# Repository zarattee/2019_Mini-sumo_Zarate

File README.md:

# 2019_Mini sumo_Zarate
 placa para robot mini sumo

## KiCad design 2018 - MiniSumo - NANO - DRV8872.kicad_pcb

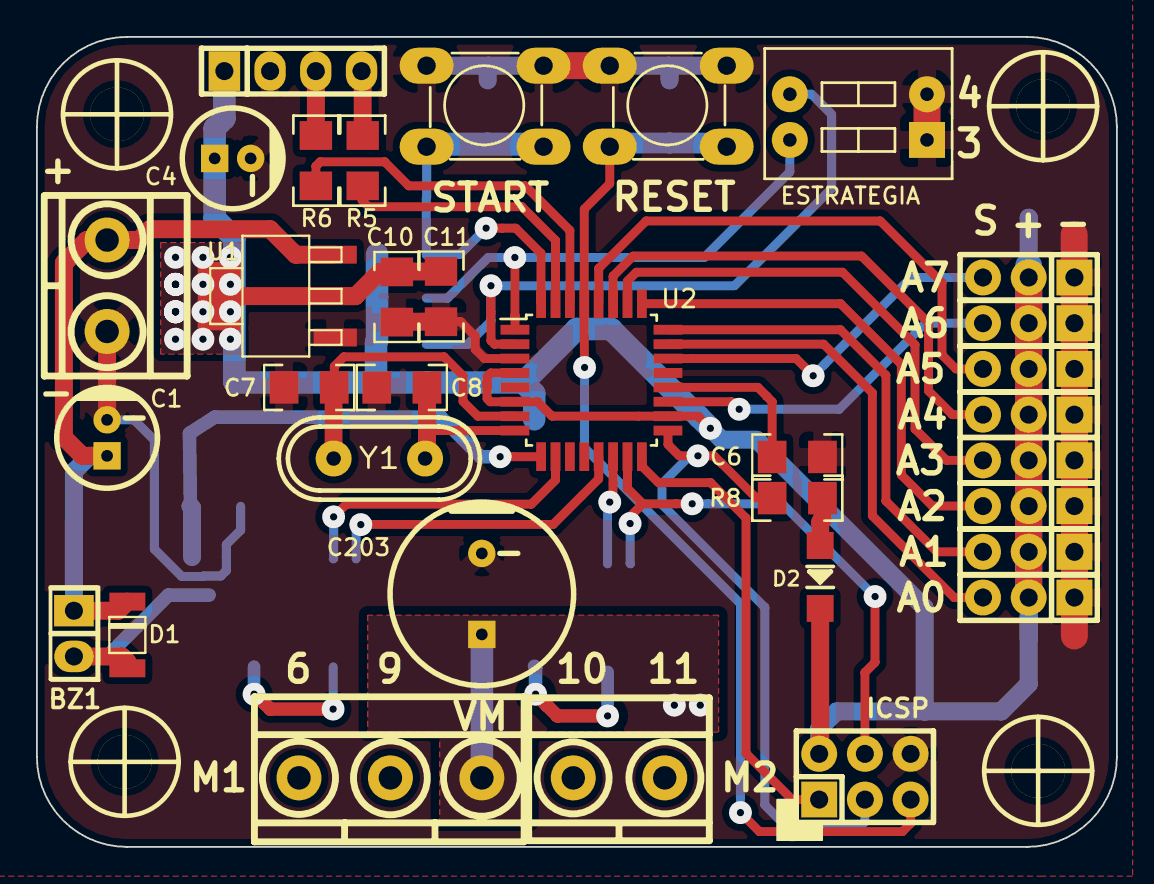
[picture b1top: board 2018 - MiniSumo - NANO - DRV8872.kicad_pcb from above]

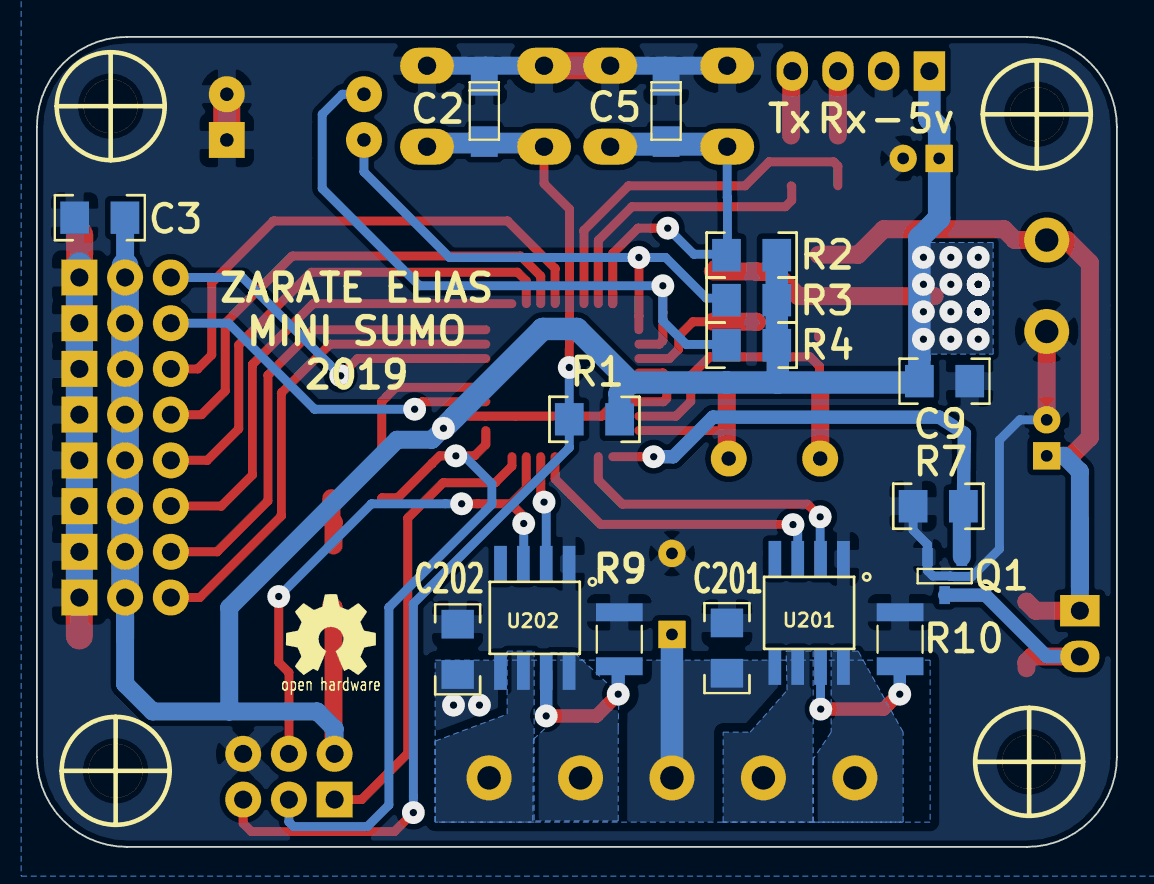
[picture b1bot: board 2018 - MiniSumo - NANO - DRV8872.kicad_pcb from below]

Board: 2 copper layers, 60.0 x 45.0 mm, 53 parts (16 on the bottom side), 38 nets.

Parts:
BZ1: Buzzer; Pin_Header_2
C1, C4: 10uF; CAP_ELEC_5x11mm
C2, C5: CAPAPOL; CAP_TAN_A
C3, C6, C201, C202: 100nF; C_1206
C7, C8, C9, C11: C; C_1206
C10: CAPAPOL; C_1206
C203: 100uF 35V; CAP_ELEC_10X8mm
D1: 1N4148; SOD80C
D2: LED; LED_1206
ESTRATEGIA: Estrategias; Dip_SW_2-300
ICSP: ICSP; pin_strip_3x2
J3: Izquierdo; Pin_Strip_3
J4: Frontal Izquierdo; Pin_Strip_3
J5: Frontal Derecho; Pin_Strip_3
J6: Derecho; Pin_Strip_3
J7: Bateria; BORNERA2_AZUL
J8: Sensor TATAMI FI; Pin_Strip_3
J9: Sensor TATAMI TI; Pin_Strip_3
J10: Sensor TATAMI TD; Pin_Strip_3
J12: Sensor TATAMI FD; Pin_Strip_3
J202: M2; BORNERA2_AZUL
Q1: 2N7002; SOT23
R1, R2, R8: R; R_1206
R3, R4: 4K7; R_1206
R5, R6: 1K; R_1206
R7: 10K; R_1206
R9, R10: Risen; PTC_1210
SW1: RESET; Pulsador_TH_4
SW2: START; Pulsador_TH_4
U1: LM1117-SOT; SOT223
U2: ATMEGA328P-AU; TQFP-32_7x7mm_Pitch0.8mm
U201, U202: DRV8872; SSOP-8
UART: Transmisor RF; pin_strip_4
VM: M1; BORNERA3_AZUL
Y1: Crystal; HC49S
hole_3mm, hole_3mm#2, hole_3mm#3, hole_3mm#4: VAL**; hole_3mm

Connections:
+5V: C3.1, C4.1, C9.2, C10.1, C11.2, D2.2, ICSP.2, J3.2, J4.2, J5.2, J6.2, J8.2, J9.2, J10.2, J12.2, R1.1, R2.1, R3.1, R4.1, U1.2, U1.4, U2.4, U2.6, U2.18, UART.1
/AUX1: ESTRATEGIA.4, R3.2, U2.1
/AUX2: ESTRATEGIA.3, R4.2, U2.2
/BUZZER: Q1.1, R7.1, U2.9
/C1: C7.2, U2.7, Y1.2
/C2: C8.2, U2.8, Y1.1
/D12/MIS0: ICSP.1, U2.16
/D13/SCK: ICSP.3, R8.1, U2.17
/DISTANCIA_D: J6.3, U2.26
/DISTANCIA_FD: J5.3, U2.25
/DISTANCIA_FI: J4.3, U2.24
/DISTANCIA_I: J3.3, U2.23
/Driver_Motores/VM: C201.1, C202.1, C203.1, U201.5, U202.5, VM.3
/M1A: U2.13, U201.3
/M1B: U2.10, U201.2
/M2A: ICSP.4, U2.15, U202.3
/M2B: U2.14, U202.2
/RESET: C2.1, ICSP.5, R1.2, SW1.3, SW1.4, U2.29
/Rx: R6.1, UART.3
/START: C5.1, R2.2, SW2.3, SW2.4, U2.32
/TATAMI_FD: J12.3, U2.27
/TATAMI_FI: J8.3, U2.28
/TATAMI_TD: J10.3, U2.22
/TATAMI_TI: J9.3, U2.19
/Tx: R5.1, UART.4
/Vin: BZ1.1, C1.1, D1.2, J7.1, U1.3
GND: C1.2, C2.2, C3.2, C4.2, C5.2, C6.2, C7.1, C8.1, C9.1, C10.2, C11.1, C201.2, C202.2, C203.2, ESTRATEGIA.1, ESTRATEGIA.2, ICSP.6, J3.1, J4.1, J5.1, J6.1, J7.2, J8.1, J9.1, J10.1, J12.1, Q1.3, R7.2, R9.2, R10.2, SW1.1, SW1.2, SW2.1, SW2.2, U1.1, U2.3, U2.5, U2.21, U201.1, U202.1, UART.2
unnamed: BZ1.2, D1.1, Q1.2
unnamed: C6.1, U2.20
unnamed: D2.1, R8.2
unnamed: U201.8, VM.1
unnamed: U201.6, VM.2
unnamed: J202.1, U202.8
unnamed: J202.2, U202.6
unnamed: R5.2, U2.31
unnamed: R6.2, U2.30
unnamed: R10.1, U201.7
unnamed: R9.1, U202.7

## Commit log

2021-01-12 se agrego lista de materiales
    se agrego lista de materiales y se saco logos
